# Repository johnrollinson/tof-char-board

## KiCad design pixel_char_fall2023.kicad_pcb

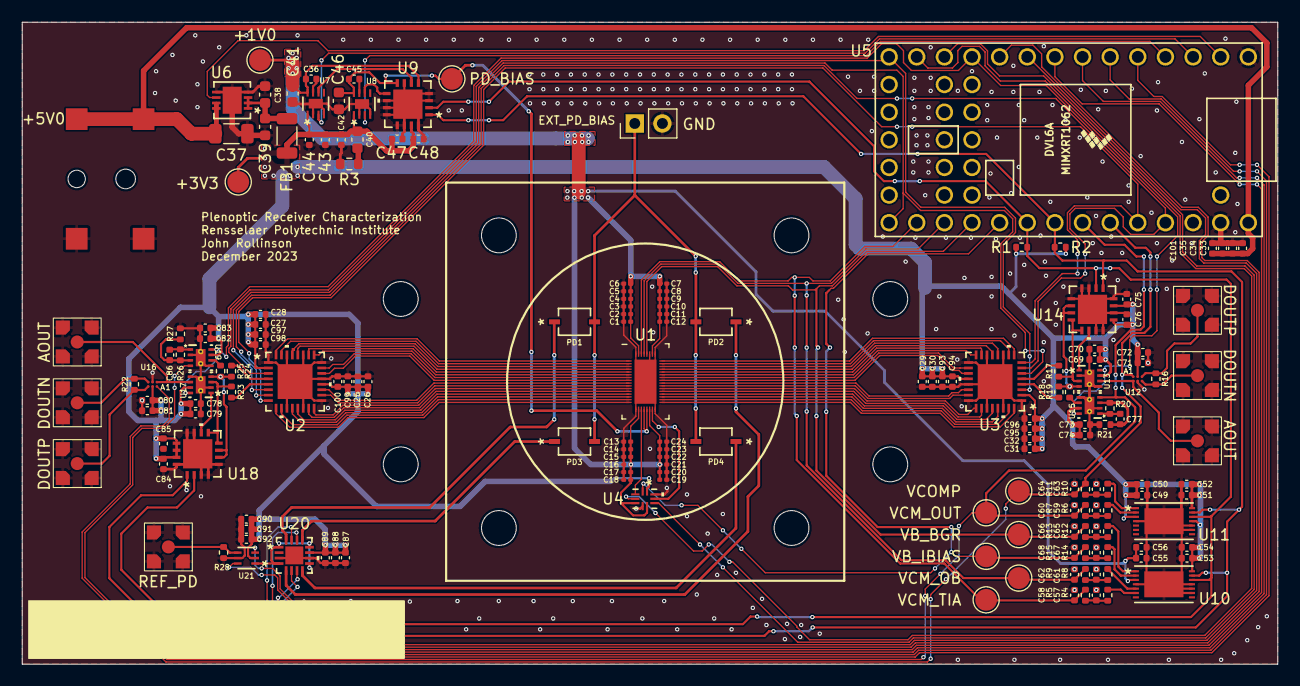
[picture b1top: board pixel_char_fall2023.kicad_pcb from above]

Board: 2 copper layers, 115.4 x 59.0 mm, 181 parts (0 on the bottom side), 110 nets.

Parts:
C1, C12, C13: 100p; C_0201_0603Metric
C2, C11, C14: 270p; C_0201_0603Metric
C3, C10, C15: 1n; C_0201_0603Metric
C4, C9, C16: 2.7n; C_0201_0603Metric
C5, C8, C17: 10n; C_0201_0603Metric
C6, C7, C18: 100n; C_0201_0603Metric
C19, C20, C21, C22, C23, C24: locked; C_0201_0603Metric
C25, C26, C27, C28, C29, C30, C31, C32, C33, C34, C35, C36, C42, C43, C44, C45, C47, C48, C49, C50, C51, C52, C53, C54, C55, C56, C63, C64, C69, C70, C71, C72, C73, C74, C75, C76, C77, C78, C79, C80, C81, C82, C83, C84, C85, C86, C87, C88, C89, C90, C91, C92, C93, C94, C95, C96, C97, C98, C99, C100, C101: locked; C_0402_1005Metric
C37: locked; C_1206_3216Metric
C38, C39, C40, C41, C46: locked; C_0603_1608Metric
C57, C58, C59, C60, C61, C62, C65, C66, C67, C68: 1u; C_0402_1005Metric
FB1: locked; L_1206_3216Metric
H1, H2, H3, H4: locked; MountingHole_3.2mm_M3
H5, H6, H7, H8: MountingHole; MountingHole_3.2mm_M3
J1, J3, J4, J5, J6, J7, J8: locked; RF12-41-T-00-50-G
J2: locked; PinHeader_1x02_P2.54mm_Vertical
J9: locked; ADC-028-1-TR-PA10T
PD1, PD2, PD3, PD4: locked; CR_D1020_VIS
R1, R2, R10, R11, R16, R17, R18, R19, R20, R21, R22, R23, R24, R25, R26, R27, R28: locked; R_0402_1005Metric
R3: locked; R_0603_1608Metric
R4, R5, R6, R7, R8, R9, R12, R13, R14, R15: 1k; R_0402_1005Metric
TP1, TP2, TP3: locked; TestPoint_Pad_D2.0mm
TP4: VCM_TIA; TestPoint_Pad_D2.0mm
TP5: VCM_OUT; TestPoint_Pad_D2.0mm
TP6: VCM_OB; TestPoint_Pad_D2.0mm
TP7: VCOMP; TestPoint_Pad_D2.0mm
TP8: VB_BGR; TestPoint_Pad_D2.0mm
TP9: VB_IBIAS; TestPoint_Pad_D2.0mm
U1: PIXEL_CHIP; pixel_bondpad
U2, U3: locked; 21-0140_T3255+4_MXM
U4: locked; 21-0028C_MXM
U5: locked; Teensy40
U6: locked; DFN-8_DD_LIT
U7, U8: locked; 21-0168E_T822-3_MXM
U9, U14, U18: locked; QFN16_4x4MC_MCH
U10, U11: locked; 21-0253_T1435N+1_MXM
U12, U16: locked; 21-100296_W60D1&plus_1_MXM
U13, U15, U17, U19: locked; DSG0008A
U20: locked; CP_16_3_ADI
U21: locked; SOT5X3-6_DRL_TEX

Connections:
+1V0: C1.1, C2.1, C3.1, C4.1, C5.1, C6.1, C7.1, C8.1, C9.1, C10.1, C11.1, C12.1, C13.1, C14.1, C15.1, C16.1, C17.1, C18.1, C19.1, C20.1, C21.1, C22.1, C23.1, C24.1, C36.1, C41.1, C55.1, C56.1, TP2.1, U1.18 (VA_1P0), U1.22 (VA_1P0), U1.42 (VA_1P0), U1.47 (VA_1P0), U4.5 (NC1), U4.7 (NC2), U7.8 (OUT), U9.5 (P1B), U10.3 (VREF)
+3V3: C25.1, C26.1, C27.1, C28.1, C29.1, C30.1, C31.1, C32.1, C40.1, C42.1, C43.1, C44.1, C47.1, C48.1, C49.1, C50.1, C51.1, C52.1, C53.1, C54.1, C69.1, C70.1, C71.1, C72.1, C73.1, C74.1, C75.1, C76.1, C78.1, C79.1, C80.1, C81.1, C82.1, C83.1, C84.1, C85.1, C87.1, C88.1, C89.1, C90.1, C91.1, C92.1, C93.1, C94.1, C95.1, C96.1, C97.1, C98.1, C99.1, C100.1, FB1.2, R1.1, R2.1, TP1.1, U2.2 (VCC), U2.20 (VCC), U3.2 (VCC), U3.20 (VCC), U4.1 (VCC), U7.1 (IN), U8.1 (IN), U9.15 (VDD), U10.14 (VCC), U11.3 (VREF), U11.11 (A0), U11.14 (VCC), U12.A2 (VCC), U13.7 (V+), U14.13 (A2), U14.15 (VDD), U15.7 (V+), U16.A2 (VCC), U17.7 (V+), U18.13 (A2), U18.14 (A1), U18.15 (VDD), U19.7 (V+), U20.11 (VDD), U21.2 (VDD)
+5V: C33.1, C34.1, C35.1, C37.1, C101.1, J9.1, U5.33 (VIN), U6.7 (IN), U6.8 (IN)
/1V0_EN: U5.3 (1_TX1_CTX2_MISO1), U7.3 (EN)
/3V3_EN: U5.2 (0_RX1_CRX2_CS1), U6.6 (*SHDN)
/AMP_EN: U5.11 (9_OUT1C), U13.8 (PD_N), U15.8 (PD_N), U17.8 (PD_N), U19.8 (PD_N)
/C0: U2.6 (C0), U3.6 (C0), U5.20 (13_SCK_CRX1_LED)
/C1: U2.7 (C1), U3.7 (C1), U5.30 (23_A9_CRX1_MCLK1)
/C2: U2.8 (C2), U3.8 (C2), U5.29 (22_A8_CTX1)
/EN_BGR: U4.8 (CB2), U5.12 (10_CS_MQSR)
/EN_IBIAS: U4.4 (CB1), U5.13 (11_MOSI_CTX1)
/Left Signal Chain/AOUT: J7.1 (In), U16.B1 (IN-), U17.6 (OUT)
/Left Signal Chain/DOUTN: J5.1 (In), R22.1, U16.B3 (OUT-)
/Left Signal Chain/DOUTP: J3.1 (In), R22.2, U16.A3 (OUT+)
/Left Signal Chain/FB: U17.1 (FB), U18.10 (P0B)
/Left Signal Chain/VINN: R23.2, U17.3 (IN-), U18.8 (P0A), U18.9 (P0W)
/Left Signal Chain/VINP: R24.2, R25.2, U17.4 (IN+), U18.6 (P1W), U18.7 (P1A)
/MP_EN: U2.3 (EN), U3.3 (EN), U5.14 (12_MISO_MQSL)
/MP_OUTNL: R23.1, U2.5 (COM1)
/MP_OUTNR: R17.1, U3.5 (COM1)
/MP_OUTPL: R24.1, U2.4 (COM0)
/MP_OUTPR: R18.1, U3.4 (COM0)
/PD1_EN: U5.5 (3_LRCLK2), U20.15 (IN1)
/PD2_EN: U5.6 (4_BCLK2), U20.14 (IN2)
/PD3_EN: U5.7 (5_IN2), U20.7 (IN3)
/PD4_EN: U5.8 (6_OUT1D), U20.6 (IN4)
/PD_BIAS: C45.1, C46.1, TP3.1, U1.20 (PD_BIAS), U1.21 (PD_BIAS), U8.8 (OUT), U9.8 (P0A)
/PD_BIAS_EN: U5.4 (2_OUT2), U8.3 (EN)
/Photodiodes/EXT_PD_BIAS: J2.1, PD1.2, PD2.2, PD3.2, PD4.2
/Photodiodes/PD1: PD1.1, U20.16 (D1)
/Photodiodes/PD2: PD2.1, U20.5 (D4)
/Photodiodes/PD3: PD3.1, U20.13 (D2)
/Photodiodes/PD4: PD4.1, U20.8 (D3)
/Photodiodes/TIA_IN: U20.1 (S1), U20.4 (S4), U20.9 (S3), U20.12 (S2), U21.1 (IN)
/Photodiodes/TIA_OUT: J1.1 (In), R28.1, U21.4 (OUT)
/Power Management/1V0_FB: U7.6 (FB), U9.6 (P1W)
/Power Management/PD_BIAS_FB: U8.6 (FB), U9.9 (P0W)
/Right Signal Chain/AOUT: J8.1 (In), U12.B1 (IN-), U13.6 (OUT)
/Right Signal Chain/DOUTN: J6.1 (In), R16.1, U12.B3 (OUT-)
/Right Signal Chain/DOUTP: J4.1 (In), R16.2, U12.A3 (OUT+)
/Right Signal Chain/FB: U13.1 (FB), U14.10 (P0B)
/Right Signal Chain/VINN: R17.2, U13.3 (IN-), U14.8 (P0A), U14.9 (P0W)
/Right Signal Chain/VINP: R18.2, R19.2, U13.4 (IN+), U14.6 (P1W), U14.7 (P1A)
/SCL: R2.2, U5.26 (19_A5_SCL0), U9.1 (SCL), U10.13 (SCL), U11.13 (SCL), U14.1 (SCL), U18.1 (SCL)
/SDA: R1.2, U5.25 (18_A4_SDA0), U9.2 (SDA), U10.12 (SDA), U11.12 (SDA), U14.2 (SDA), U18.2 (SDA)
/TIA_EN: U5.9 (7_RX2_OUT1A), U21.3 (*EN)
/TIA_IDC_EN: U5.10 (8_TX2_IN1), U21.6 (*IDC_EN)
/VA_BGR: U1.23 (VA_BGR), U4.9 (COM2)
/VB_BGR: C66.1, R13.2, TP8.1, U1.44 (VB_BGR), U5.23 (16_A2_RX4_SCL1)
/VB_IBIAS: U1.19 (VB_IBIAS), U4.3 (COM1)
/VB_IBIAS_DAC: C68.1, R15.2, TP9.1, U4.2 (NO1), U5.24 (17_A3_TX4_SDA1)
/VCM_OB: C62.1, R9.2, TP6.1, U1.45 (VCM_OB), U5.22 (15_A1_RX3_SPDIF_IN)
/VCM_OUT_DAC: C60.1, R7.2, TP5.1, U5.27 (20_A6_TX5_LRCLK1), U15.4 (IN+), U19.4 (IN+)
/VCM_TIA: C58.1, R5.2, TP4.1, U1.46 (VCM_TIA), U5.21 (14_A0_TX3_SPDIF_OUT)
/VCOMP: C64.1, R11.2, TP7.1, U5.28 (21_A7_RX5_BCLK1), U12.A1 (IN+), U16.A1 (IN+)
/VN0: U1.39 (VN0), U3.10 (D0_1)
/VN1: U1.37 (VN1), U3.13 (D1_1)
/VN2: U1.35 (VN2), U3.16 (D2_1)
/VN3: U1.33 (VN3), U3.19 (D3_1)
/VN4: U1.31 (VN4), U3.23 (D4_0)
/VN5: U1.29 (VN5), U3.26 (D5_0)
/VN6: U1.27 (VN6), U3.29 (D6_0)
/VN7: U1.25 (VN7), U3.32 (D7_0)
/VN8: U1.2 (VN8), U2.31 (D7_1)
/VN9: U1.4 (VN9), U2.28 (D6_1)
/VN10: U1.6 (VN10), U2.25 (D5_1)
/VN11: U1.8 (VN11), U2.22 (D4_1)
/VN12: U1.10 (VN12), U2.18 (D3_0)
/VN13: U1.12 (VN13), U2.15 (D2_0)
/VN14: U1.14 (VN14), U2.12 (D1_0)
/VN15: U1.16 (VN15), U2.9 (D0_0)
/VP0: U1.40 (VP0), U3.9 (D0_0)
/VP1: U1.38 (VP1), U3.12 (D1_0)
/VP2: U1.36 (VP2), U3.15 (D2_0)
/VP3: U1.34 (VP3), U3.18 (D3_0)
/VP4: U1.32 (VP4), U3.22 (D4_1)
/VP5: U1.30 (VP5), U3.25 (D5_1)
/VP6: U1.28 (VP6), U3.28 (D6_1)
/VP7: U1.26 (VP7), U3.31 (D7_1)
/VP8: U1.1 (VP8), U2.32 (D7_0)
/VP9: U1.3 (VP9), U2.29 (D6_0)
/VP10: U1.5 (VP10), U2.26 (D5_0)
/VP11: U1.7 (VP11), U2.23 (D4_0)
/VP12: U1.9 (VP12), U2.19 (D3_1)
/VP13: U1.11 (VP13), U2.16 (D2_1)
/VP14: U1.13 (VP14), U2.13 (D1_1)
/VP15: U1.15 (VP15), U2.10 (D0_1)
GND: C1.2, C2.2, C3.2, C4.2, C5.2, C6.2, C7.2, C8.2, C9.2, C10.2, C11.2, C12.2, C13.2, C14.2, C15.2, C16.2, C17.2, C18.2, C19.2, C20.2, C21.2, C22.2, C23.2, C24.2, C25.2, C26.2, C27.2, C28.2, C29.2, C30.2, C31.2, C32.2, C33.2, C34.2, C35.2, C37.2, C38.2, C39.2, C41.2, C42.2, C43.2, C44.2, C46.2, C47.2, C48.2, C49.2, C50.2, C51.2, C52.2, C53.2, C54.2, C55.2, C56.2, C57.2, C58.2, C59.2, C60.2, C61.2, C62.2, C63.2, C64.2, C65.2, C66.2, C67.2, C68.2, C69.2, C70.2, C71.2, C72.2, C73.2, C74.2, C75.2, C76.2, C78.2, C79.2, C80.2, C81.2, C82.2, C83.2, C84.2, C85.2, C87.2, C88.2, C89.2, C90.2, C91.2, C92.2, C93.2, C94.2, C95.2, C96.2, C97.2, C98.2, C99.2, C100.2, C101.2, J1.2 (Ext), J2.2, J3.2 (Ext), J4.2 (Ext), J5.2 (Ext), J6.2 (Ext), J7.2 (Ext), J8.2 (Ext), J9.2, J9.3, R3.2, R21.1, R27.1, R28.2, U1.17 (VA_GND), U1.24 (VA_GND), U1.41 (VA_GND), U1.43 (VA_GND), U1.48 (VA_GND), U1.49 (VA_GND), U2.1 (GND), U2.11 (GND), U2.14 (GND), U2.17 (GND), U2.21 (GND), U2.24 (GND), U2.27 (GND), U2.30 (GND), U2.33 (EPAD), U3.1 (GND), U3.11 (GND), U3.14 (GND), U3.17 (GND), U3.21 (GND), U3.24 (GND), U3.27 (GND), U3.30 (GND), U3.33 (EPAD), U4.6 (GND), U4.10 (NO2), U5.1 (GND), U5.32 (GND), U6.4 (GND), U6.5 (GND), U6.9 (EPAD), U7.2 (GND), U7.4 (GS), U7.9 (EPAD), U8.2 (GND), U8.4 (GS), U8.9 (EPAD), U9.3 (VSS), U9.4 (VSS), U9.7 (P1A), U9.10 (P0B), U9.11 (NC(G)), U9.12 (*WP), U9.13 (A2), U9.14 (A1), U9.16 (HVC/A0), U9.17 (EP), U10.4 (GND), U10.9 (GND), U10.10 (A1), U10.11 (A0), U10.15 (EPAD), U11.4 (GND), U11.9 (GND), U11.10 (A1), U11.15 (EPAD), U12.B2 (GND), U13.2 (VS-), U13.5 (VS-), U13.9 (DAP), U14.3 (VSS), U14.4 (VSS), U14.5 (P1B), U14.11 (NC(G)), U14.12 (*WP), U14.14 (A1), U14.16 (HVC/A0), U14.17 (EP), U15.2 (VS-), U15.5 (VS-), U15.9 (DAP), U16.B2 (GND), U17.2 (VS-), U17.5 (VS-), U17.9 (DAP), U18.3 (VSS), U18.4 (VSS), U18.5 (P1B), U18.11 (NC(G)), U18.12 (*WP), U18.16 (HVC/A0), U18.17 (EP), U19.2 (VS-), U19.5 (VS-), U19.9 (DAP), U20.3 (GND), U20.10 (NC), U20.17 (EP), U21.5 (GND)
unnamed: C40.2, R3.1
unnamed: C57.1, R4.2, R5.1
unnamed: C59.1, R6.2, R7.1
unnamed: C61.1, R8.2, R9.1
unnamed: C63.1, R10.2, R11.1
unnamed: C65.1, R12.2, R13.1
unnamed: C67.1, R14.2, R15.1
unnamed: C38.1, C39.1, FB1.1, U6.1 (OUT), U6.2 (OUT), U6.3 (SENSE/ADJ)
unnamed: C36.2, U7.7 (BYP)
unnamed: C45.2, U8.7 (BYP)
unnamed: R12.1, U10.1 (DAC0)
unnamed: R14.1, U10.2 (DAC1)
unnamed: R8.1, U10.5 (DAC2)
unnamed: R4.1, U10.6 (DAC3)
unnamed: R10.1, U11.1 (DAC0)
unnamed: R6.1, U11.2 (DAC1)
unnamed: C77.2, R20.1, U15.1 (FB)
unnamed: C77.1, R20.2, R21.2, U15.3 (IN-)
unnamed: R19.1, U15.6 (OUT)
unnamed: C86.2, R26.1, U19.1 (FB)
unnamed: C86.1, R26.2, R27.2, U19.3 (IN-)
unnamed: R25.1, U19.6 (OUT)

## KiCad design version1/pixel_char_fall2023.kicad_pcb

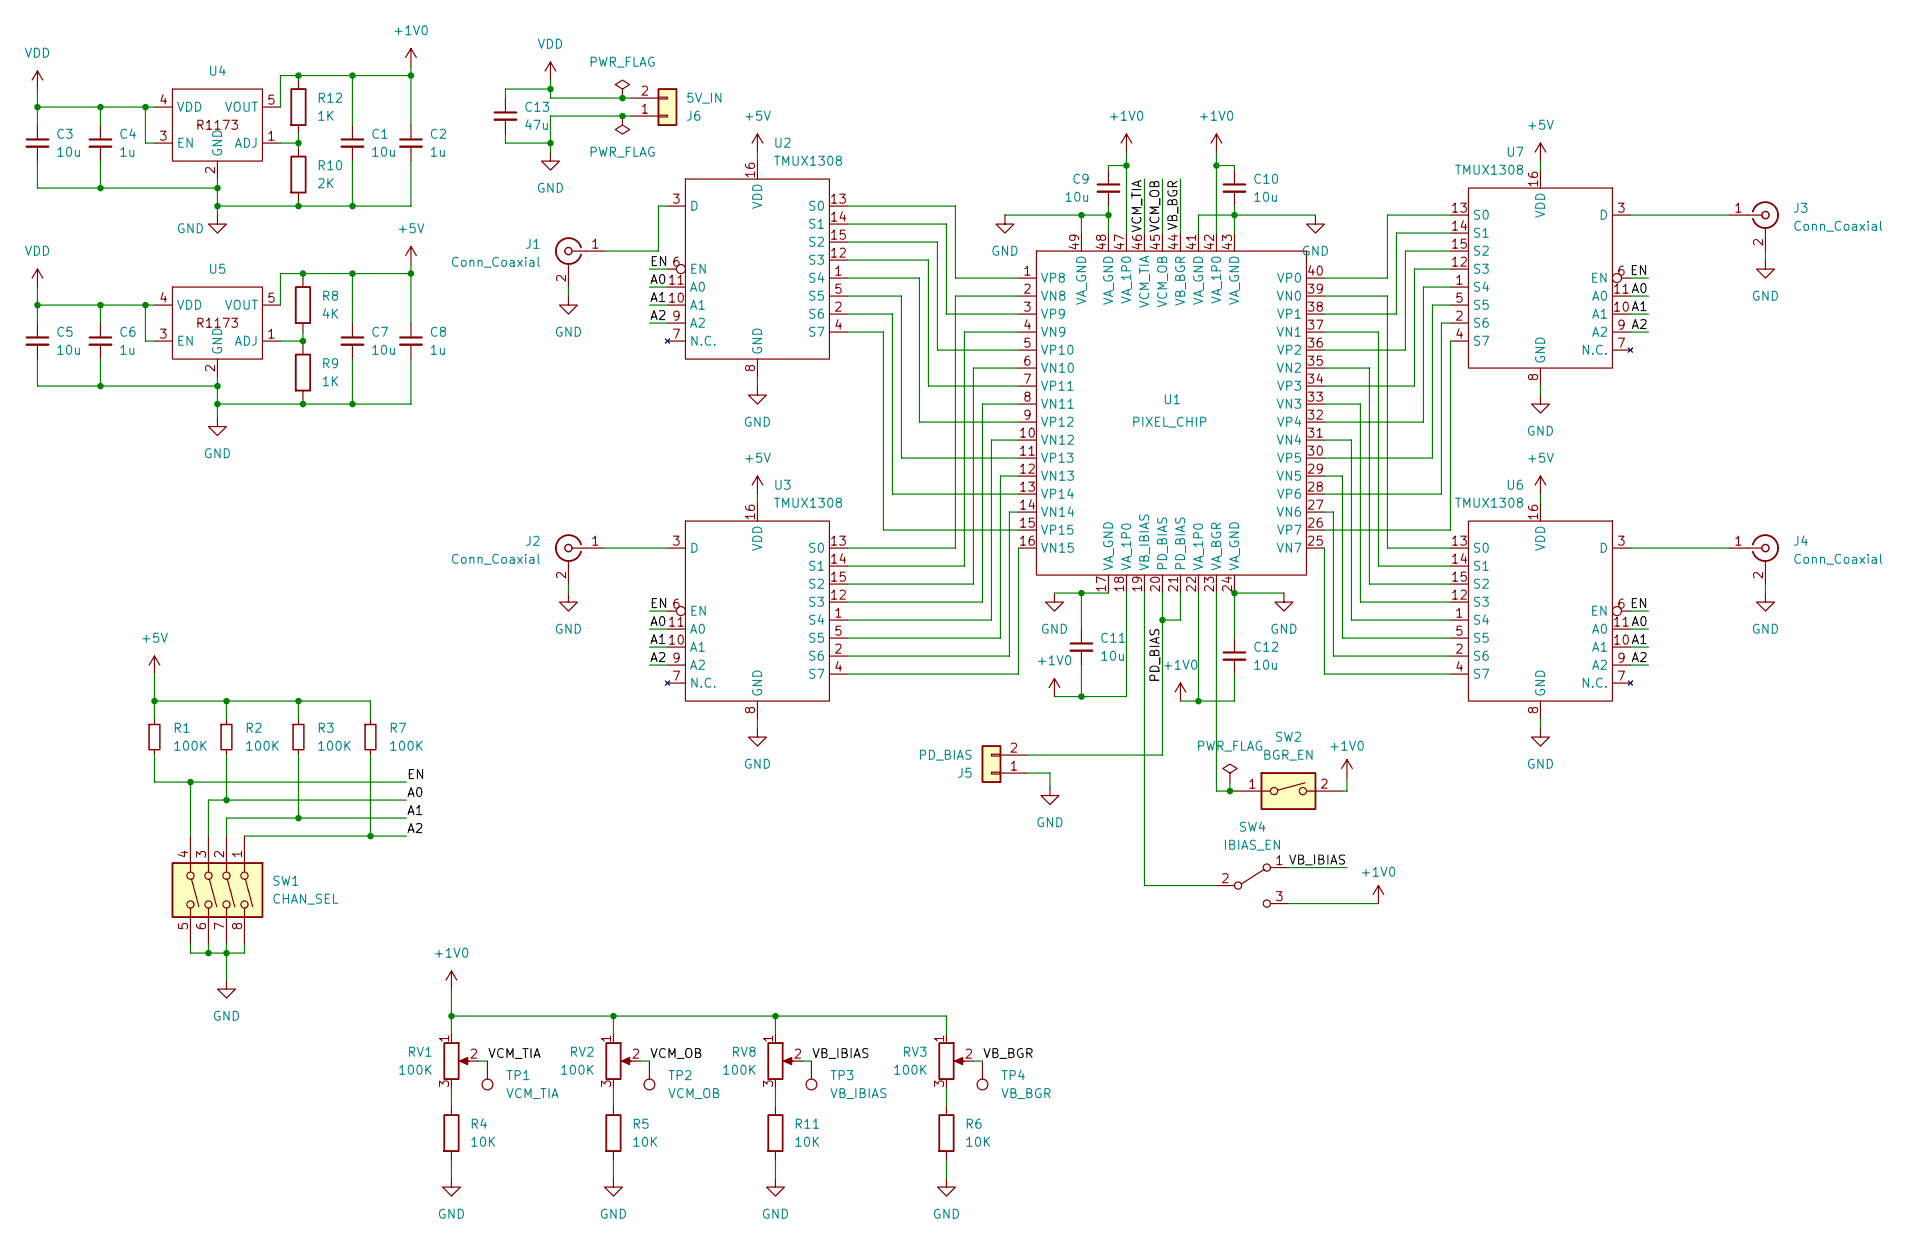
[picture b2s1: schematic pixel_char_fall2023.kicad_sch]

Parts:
C1, C3, C5, C7, C9, C10, C11, C12: 10u; C_0603_1608Metric
C2, C4, C6, C8: 1u; C_0603_1608Metric
C13: 47u; C_0603_1608Metric
J1, J2, J3, J4: Conn_Coaxial; SMA_Molex_73251-1153_EdgeMount_Horizontal
J5: PD_BIAS; PinHeader_1x02_P2.54mm_Vertical
J6: 5V_IN; PinHeader_1x02_P2.54mm_Vertical
R1, R2, R3, R7: 100K; R_0603_1608Metric
R4, R5, R6, R11: 10K; R_0603_1608Metric
R8: 4K; R_0603_1608Metric
R9, R12: 1K; R_0603_1608Metric
R10: 2K; R_0603_1608Metric
RV1, RV2, RV3, RV8: 100K; bourns_3361P
SW1: CHAN_SEL; SW_DIP_SPSTx04_Slide_6.7x11.72mm_W6.73mm_P2.54mm_LowProfile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
SW2: BGR_EN; SW_DIP_SPSTx01_Slide_6.7x4.1mm_W6.73mm_P2.54mm_LowProfile_J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
SW4: IBIAS_EN; nidec_spdt_jhook
TP1: VCM_TIA; TestPoint_Pad_D2.0mm
TP2: VCM_OB; TestPoint_Pad_D2.0mm
TP3: VB_IBIAS; TestPoint_Pad_D2.0mm
TP4: VB_BGR; TestPoint_Pad_D2.0mm
U1: PIXEL_CHIP; pixel_bondpad
U2, U3, U6, U7: TMUX1308; sot-23-thin-16
U4, U5: SOT-89-5

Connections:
+1V0: C1.1, C2.1, C9.1, C10.1, C11.2, C12.2, R12.1, RV1.1, RV2.1, RV3.1, RV8.1, SW2.2, SW4.3 (C), U1.18 (VA_1P0), U1.22 (VA_1P0), U1.42 (VA_1P0), U1.47 (VA_1P0), U4.5 (VOUT)
+5V: C7.1, C8.1, R1.1, R2.1, R3.1, R7.1, R8.1, U2.16 (VDD), U3.16 (VDD), U5.5 (VOUT), U6.16 (VDD), U7.16 (VDD)
/A0: R2.2, SW1.3, U2.11 (A0), U3.11 (A0), U6.11 (A0), U7.11 (A0)
/A1: R3.2, SW1.2, U2.10 (A1), U3.10 (A1), U6.10 (A1), U7.10 (A1)
/A2: R7.2, SW1.1, U2.9 (A2), U3.9 (A2), U6.9 (A2), U7.9 (A2)
/EN: R1.2, SW1.4, U2.6 (EN), U3.6 (EN), U6.6 (EN), U7.6 (EN)
/PD_BIAS: J5.2, U1.20 (PD_BIAS), U1.21 (PD_BIAS)
/VB_BGR: RV3.2, TP4.1, U1.44 (VB_BGR)
/VB_IBIAS: RV8.2, SW4.1 (A), TP3.1
/VCM_OB: RV2.2, TP2.1, U1.45 (VCM_OB)
/VCM_TIA: RV1.2, TP1.1, U1.46 (VCM_TIA)
GND: C1.2, C2.2, C3.2, C4.2, C5.2, C6.2, C7.2, C8.2, C9.2, C10.2, C11.1, C12.1, C13.2, J1.2 (Ext), J2.2 (Ext), J3.2 (Ext), J4.2 (Ext), J5.1, J6.1, R4.2, R5.2, R6.2, R9.2, R10.2, R11.2, SW1.5, SW1.6, SW1.7, SW1.8, U1.17 (VA_GND), U1.24 (VA_GND), U1.41 (VA_GND), U1.43 (VA_GND), U1.48 (VA_GND), U1.49 (VA_GND), U2.8 (GND), U3.8 (GND), U4.2 (GND), U5.2 (GND), U6.8 (GND), U7.8 (GND)
unnamed: J1.1 (In), U2.3 (D)
unnamed: J2.1 (In), U3.3 (D)
unnamed: J3.1 (In), U7.3 (D)
unnamed: J4.1 (In), U6.3 (D)
unnamed: R4.1, RV1.3
unnamed: R5.1, RV2.3
unnamed: R6.1, RV3.3
unnamed: R11.1, RV8.3
unnamed: SW4.2 (B), U1.19 (VB_IBIAS)
unnamed: SW2.1, U1.23 (VA_BGR)
unnamed: U1.39 (VN0), U6.13 (S0)
unnamed: U1.37 (VN1), U6.14 (S1)
unnamed: U1.35 (VN2), U6.15 (S2)
unnamed: U1.33 (VN3), U6.12 (S3)
unnamed: U1.31 (VN4), U6.1 (S4)
unnamed: U1.29 (VN5), U6.5 (S5)
unnamed: U1.27 (VN6), U6.2 (S6)
unnamed: U1.25 (VN7), U6.4 (S7)
unnamed: U1.2 (VN8), U3.13 (S0)
unnamed: U1.4 (VN9), U3.14 (S1)
unnamed: U1.6 (VN10), U3.15 (S2)
unnamed: U1.8 (VN11), U3.12 (S3)
unnamed: U1.10 (VN12), U3.1 (S4)
unnamed: U1.12 (VN13), U3.5 (S5)
unnamed: U1.14 (VN14), U3.2 (S6)
unnamed: U1.16 (VN15), U3.4 (S7)
unnamed: U1.40 (VP0), U7.13 (S0)
unnamed: U1.38 (VP1), U7.14 (S1)
unnamed: U1.36 (VP2), U7.15 (S2)
unnamed: U1.34 (VP3), U7.12 (S3)
unnamed: U1.32 (VP4), U7.1 (S4)
unnamed: U1.30 (VP5), U7.5 (S5)
unnamed: U1.28 (VP6), U7.2 (S6)
unnamed: U1.26 (VP7), U7.4 (S7)
unnamed: U1.1 (VP8), U2.13 (S0)
unnamed: U1.3 (VP9), U2.14 (S1)
unnamed: U1.5 (VP10), U2.15 (S2)
unnamed: U1.7 (VP11), U2.12 (S3)
unnamed: U1.9 (VP12), U2.1 (S4)
unnamed: U1.11 (VP13), U2.5 (S5)
unnamed: U1.13 (VP14), U2.2 (S6)
unnamed: U1.15 (VP15), U2.4 (S7)
unnamed: R10.1, R12.2, U4.1 (ADJ)
unnamed: R8.2, R9.1, U5.1 (ADJ)
VDD: C3.1, C4.1, C5.1, C6.1, C13.1, J6.2, U4.3 (EN), U4.4 (VDD), U5.3 (EN), U5.4 (VDD)

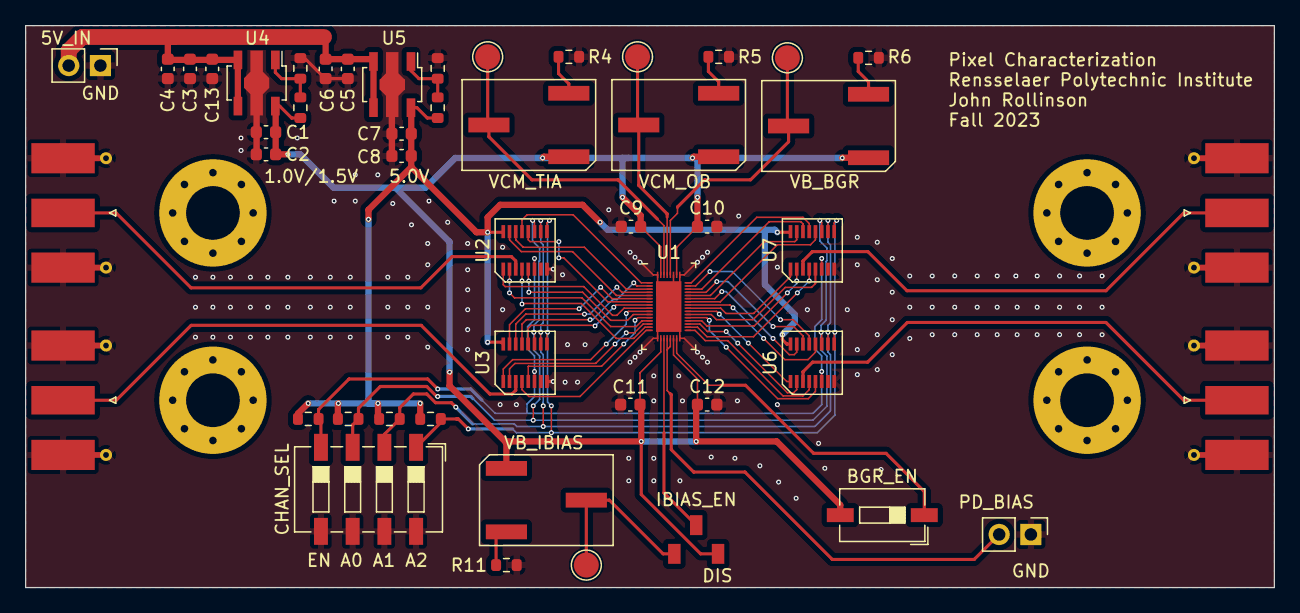
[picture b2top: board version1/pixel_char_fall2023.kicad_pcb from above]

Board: 2 copper layers, 100.0 x 45.0 mm, 49 parts (0 on the bottom side), 57 nets.

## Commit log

2024-03-30 adding gitignore
2024-03-30 removed untracked files
